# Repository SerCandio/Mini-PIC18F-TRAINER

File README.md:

# Mini-PIC18F-TRAINER
Tarjeta entrenadora de desarrollo básica con pines libres GPIO, puerto USB CDC Host , pines de programación para PICKIT3 ICSP seleccionables como se muestra a continuacion:

<B><I>Figura 1.- Vista general de la entrenadora basica de PIC</I></B>

<h2 dir="auto" tabindex="-1">DESCRIPCION Y CARACTERISTICAS</h2>
<P>Puede visualizar una referencia del plano esquematico de la PCB aqui: <B><A HREF="https://github.com/SerCandio/Mini-PIC18F-TRAINER/blob/main/Esquemas%20Schematic/Min_PIC_Trailer_PDF_BN.pdf">Min_PIC_Trailer_PDF_BN.pdf</A></B></P>

<B>1.-Entrada de Voltaje</B>

La placa Mini-PIC18F-TRAINER se alimenta desde la bornera verde +5V utilizando una fuente externa. No debe usar otro voltaje diferente de 4.9 ~ 5.0 V

<B>2.-Oscilador primario XTAL</B>

Entre los pines OSC1 y OSC2 (RA7 y RA6) esta conectado un cristal de cuarzo de 16MHz para una mayor exactitud en la base de tiempo del ciclo de instruccion(<B>4/FOSC</B>), siendo de rapida ejecucion Aunque este puede ser cambiado por otros cristales de menor frecuencia, un XTAL de 16MHz permite usar todos los perifericos incluido el puerto <B>USB</B> que require una frecuencia derivada de <B>48MHz</B> para alta velocidad(<B>HIGH Speed</B>) y otra de 6MHz para baja velocidad (<B>LOW Speed</B>)

<B>3.-Oscilador secundario</B>

Entre los pines SOSCO y SOSCI (RC0 y RC1) esta conectado un cristal de 32.768KHz que alimenta el temporizador 1 o TIMER 1 del microcontrador PIC18F. Permite un calculo preciso de bases de tiempo real de 1 segundo o submultiplos (ex. 1ms) , lo que es de utilidad para la temporizacion de tareas cuando se trabaja con RTOS (ver <B><A HREF="https://github.com/SerCandio/Microcontrolador-PIC18F/blob/main/LIBRERIAS%20PIC18/RTOS.h">Libreria RTOS</A></B>) dado que incluso en modo SLEEP puede temporizar eventos de interrupcion donde se despierta la CPU (ver <B><A HREF="https://github.com/SerCandio/Microcontrolador-PIC18F/blob/main/LIBRERIAS%20PIC18/TMR1.h">Libreria Timer 1</A></B>)

<B>4.-Boton de RESET</B>

Se utiliza para re-iniciar el programa en ejecucion. Esta etiquetado como <B>RESET</B>. Esta entrada esta compartida con el PICKIT3 -- > MCLR

<B>5.-LED indicador encendido</B>

Este LED1 de color verde nos indica que la tarjeta por consiguiente el microcontrolador PIC esta siendo aliementado. 

<B>6.-Conector USB Mini Type B </B>

Este USB plug esta directamente conectado a los pines  <B>D+</B> y <B>D-</B> o 24 y 23 del PIC18F. Provee una interfaz de comunicacion de alta velocidad tipo USB- CDC del PIC con la PC que puede actuar como host. Tenga en cuenta que este tipo de comunicacion se monta en un puerto COM de la PC como si se tratase de comunicacion serie UART . 

En este <B><A HREF="https://www.usb.org/">Link</A></B> se habla mas acerca de la especificacion USB.

<B>7.-Pines de programacion ICSP</B>

El DIP SWITCH SW1 permite dar salida a los pines de programacion mediante la PICKIT3 de encontrarse en la posicion ON. Si no se require re-programar pueden permanecer en OFF , quedando asi protejidos frente a contactos externos no deseados

<B>8.-LED de prueba enchufable</B>

Este USER LED de color azul puede ser conectado  directamente  al pin RD0 si se coloca el jumper encima, permite hacer codigos de prueba (ex. blinkeo ON/OFF), como bandera de error o algun otro uso personalizado que el usuario le pueda dar.

<B>9.-JUMPER Selector de Volaje</B>

Este jumper de tipo <B><I>pin header</I></B> es capaz de seleccionar el voltaje de suministro, la tarjeta <B>Mini-PIC18F Trainer</B> para que sea alimentado por fuente externa (bornera color verde), por la PICKIT 3 o por el USB proveniente de la PC. En nuestro caso :

- Alimentacion por fuente externa (<B>SI</B>)
- Alimentacion por PICKIT (<B>SI</B>)
- Alimentacion por USB (<B>NO</B>)

<h2 dir="auto" tabindex="-1">PRECAUCION </h2>

Debe asegurarse que el PICKIT 3 actue como sensor de voltaje en su pin <B><I>VDD</I></B> haciendo en MPLAB (IDE /IPE) como se muestra:

<B><I>Figura 2.- Opciones de alimentacion del apartado "POWER" del IDE</I></B>
<p>Asegurese que la opcion <B><I>Power Tarjet from PICkit3</B></I> este deshabilitada. Caso contrario, podria dañarse el programador o incluso la PC.</p>

<h2 dir="auto" tabindex="-1">COMPONENTES EN PLACA(Descripcion grafica)</h2> 

Podemos visualizar de forma grafica los compoentes en placa incorporados en nuesta entrenadora Mini de PIC18 :

<center><B><I>Figura 3.- Componentes basicos: entrenadora basica de PIC</I></B></center>

<h2 dir="auto" tabindex="-1">PRUEBAS Y FUNCIONAMIENTO</h2>
En el siguiente <B><A HREF="https://youtu.be/mNRTedm4bW8">video</A></B> incrustado podemos ver una prueba de funcionamiento de la placa entrenadora(orientado a MultiTasking RTOS):

Si deseamos los archivos de codigo fuente con puerto USB incluido, se encuentran <B><A HREF="https://github.com/SerCandio/Microcontrolador-PIC18F">aqui</A></B> :

<h2 dir="auto" tabindex="-1">Nota</h2>
Los archivos de proyecto de EAGLE para poder modificar y/o manufacturar esta PCB estan <B><A HREF="https://github.com/SerCandio/Mini-PIC18F-TRAINER/tree/main/EAGLE%20CAD%20FILES">aqui</A></B>
<h2 dir="auto" tabindex="-1">AUTOR</h2>
- Candiotti L. Sergio (Lima, Peru)

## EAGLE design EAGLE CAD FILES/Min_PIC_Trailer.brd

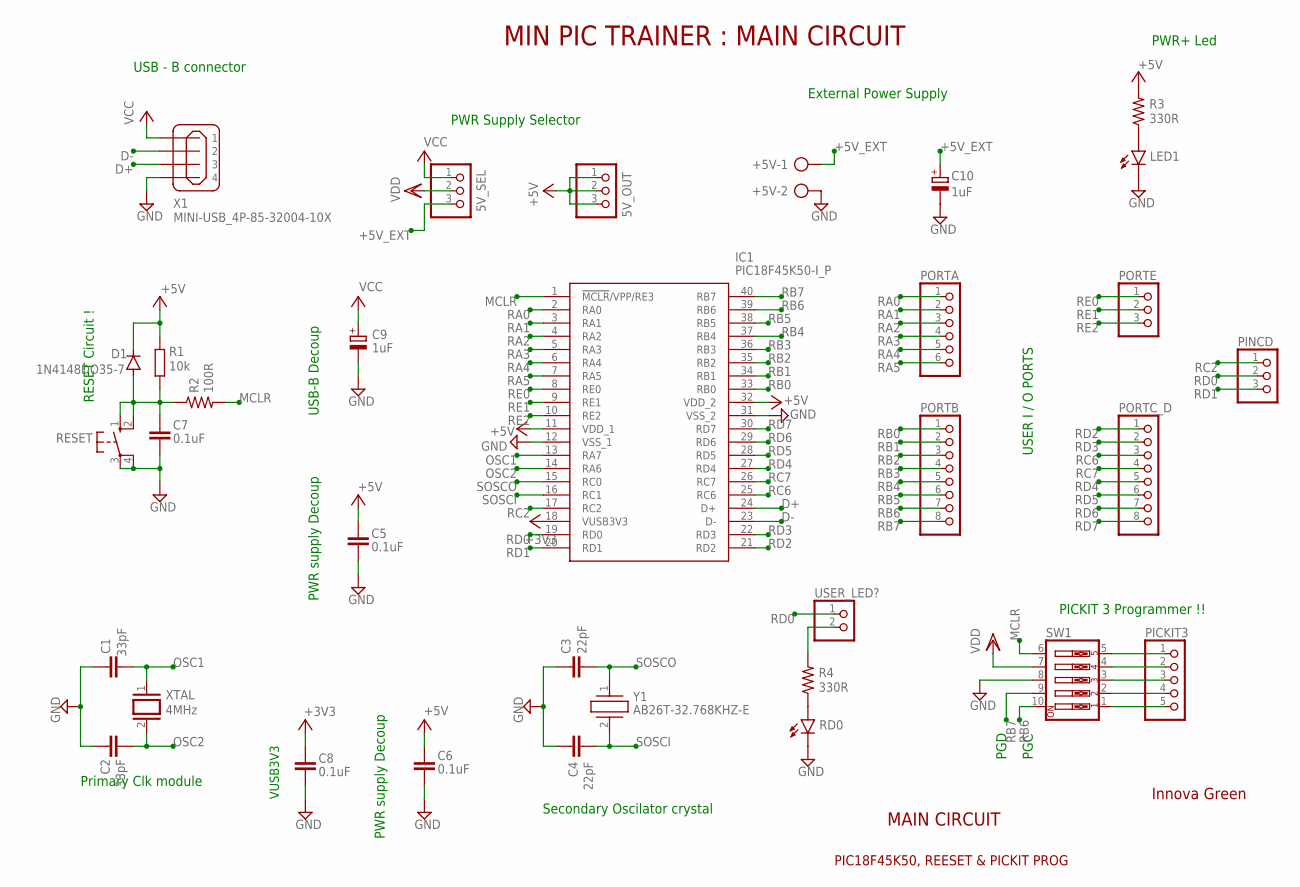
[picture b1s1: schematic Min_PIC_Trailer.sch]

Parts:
5V_OUT, 5V_SEL: PINHD-1X3; 1X03
+5V: AK500/2
C1, C2: 33pF; C0805
C3, C4: 22pF; C0805K
C5, C6, C7, C8: 0.1uF; C0805
C9, C10: 1uF; E2,5-6
D1: 1N4148DO35-7; DO35-7
IC1: PIC18F45K50-I_P; DIP1543W58P254L5175H635Q40N
LED1: LEDCHIP-LED0805; CHIP-LED0805
PICKIT3: PINHD-1X5/90; 1X05/90
PINCD: PINHD-1X3; 1X03
PORTA: PINHD-1X6; 1X06
PORTB: PINHD-1X8; 1X08
PORTC_D: PINHD-1X8; 1X08
PORTE: PINHD-1X3; 1X03
R1: 10k; R0805
R2: 100R; R0805W
R3, R4: 330R; R0805
RD0: LEDCHIP-LED0805; CHIP-LED0805
RESET: 10-XX; B3F-10XX
SW1: SW_DIP-5; EDG-05
USER_LED?: PINHD-1X2; 1X02
X1: MINI-USB_4P-85-32004-10X; 85-32004-10X
XTAL: 4MHz; QS
Y1: AB26T-32.768KHZ-E; AB26T32768KHZE

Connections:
+3V3: C8.1, IC1.18 (VUSB3V3)
+5V: 5V_OUT.1, 5V_OUT.2, 5V_OUT.3, C5.1, C6.1, D1.C, IC1.11 (VDD_1), IC1.32 (VDD_2), R1.2, R3.2
+5V_EXT: 5V_SEL.3, +5V.1, C10.+
D+: IC1.24 (D+), X1.3
D-: IC1.23 (D-), X1.2
GND: +5V.2, C1.1, C2.1, C3.1, C4.1, C5.2, C6.2, C7.2, C8.2, C9.-, C10.-, IC1.12 (VSS_1), IC1.31 (VSS_2), LED1.C, RD0.C, RESET.3, RESET.4 (P1), SW1.8, X1.4
MCLR: IC1.1 (!MCLR!/VPP/RE3), R2.2, SW1.6
unnamed: C7.1, D1.A, R1.1, R2.1, RESET.1 (S), RESET.2 (S1)
unnamed: PICKIT3.1, SW1.5
unnamed: PICKIT3.2, SW1.4
unnamed: PICKIT3.3, SW1.3
unnamed: PICKIT3.4, SW1.2
unnamed: PICKIT3.5, SW1.1
unnamed: LED1.A, R3.1
unnamed: R4.1, RD0.A
unnamed: R4.2, USER_LED?.2
OSC1: C1.2, IC1.13 (RA7), XTAL.1
OSC2: C2.2, IC1.14 (RA6), XTAL.2
RA0: IC1.2 (RA0), PORTA.1
RA1: IC1.3 (RA1), PORTA.2
RA2: IC1.4 (RA2), PORTA.3
RA3: IC1.5 (RA3), PORTA.4
RA4: IC1.6 (RA4), PORTA.5
RA5: IC1.7 (RA5), PORTA.6
RB0: IC1.33 (RB0), PORTB.1
RB1: IC1.34 (RB1), PORTB.2
RB2: IC1.35 (RB2), PORTB.3
RB3: IC1.36 (RB3), PORTB.4
RB4: IC1.37 (RB4), PORTB.5
RB5: IC1.38 (RB5), PORTB.6
RB6: IC1.39 (RB6), PORTB.7, SW1.10
RB7: IC1.40 (RB7), PORTB.8, SW1.9
RC2: IC1.17 (RC2), PINCD.1
RC6: IC1.25 (RC6), PORTC_D.3
RC7: IC1.26 (RC7), PORTC_D.4
RD0: IC1.19 (RD0), PINCD.2, USER_LED?.1
RD1: IC1.20 (RD1), PINCD.3
RD2: IC1.21 (RD2), PORTC_D.1
RD3: IC1.22 (RD3), PORTC_D.2
RD4: IC1.27 (RD4), PORTC_D.5
RD5: IC1.28 (RD5), PORTC_D.6
RD6: IC1.29 (RD6), PORTC_D.7
RD7: IC1.30 (RD7), PORTC_D.8
RE0: IC1.8 (RE0), PORTE.1
RE1: IC1.9 (RE1), PORTE.2
RE2: IC1.10 (RE2), PORTE.3
SOSCI: C4.2, IC1.16 (RC1), Y1.2
SOSCO: C3.2, IC1.15 (RC0), Y1.1
VCC: 5V_SEL.1, C9.+, X1.1
VDD: 5V_SEL.2, SW1.7

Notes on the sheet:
VUSB3V3
PWR Supply Selector
USB-B Decoup
PICKIT 3 Programmer !!
PWR supply Decoup
Primary Clk module
Secondary Oscilator crystal
PGD
PGC
External Power Supply
PWR+ Led
USER I / O PORTS
RESET Circuit !
USB - B connector
MIN PIC TRAINER : MAIN CIRCUIT
MAIN CIRCUIT
PIC18F45K50, REESET & PICKIT PROG
Innova Green

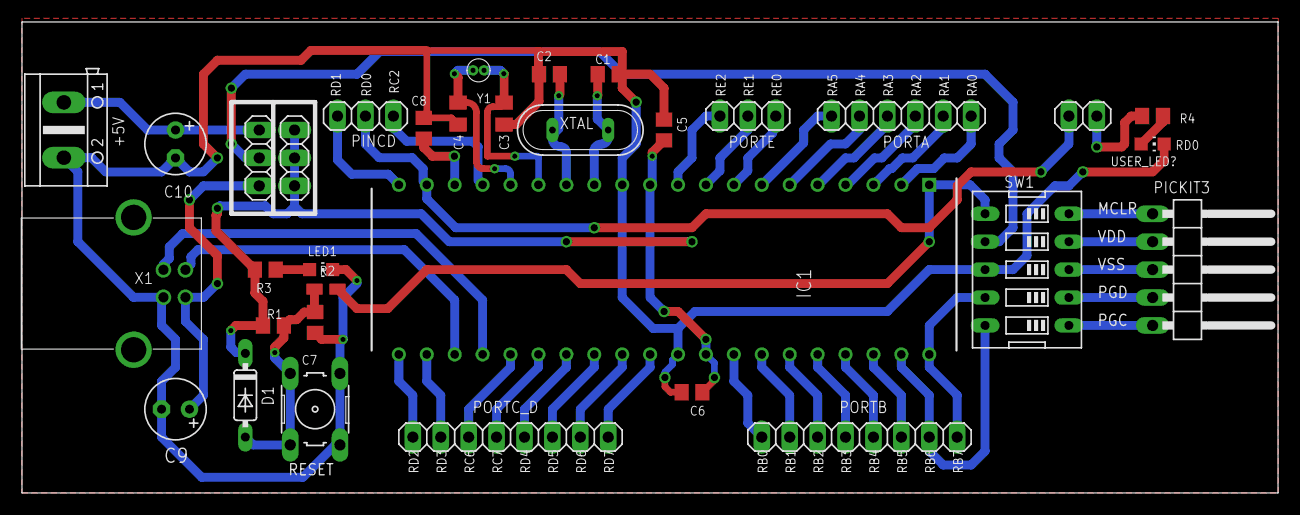
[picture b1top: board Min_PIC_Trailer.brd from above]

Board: 2 copper layers, 114.3 x 42.9 mm, 33 parts (0 on the bottom side), 50 nets.
